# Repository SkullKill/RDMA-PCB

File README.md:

# RDMA-PCB
Rpi Dead Man Alarm - PCB and 3D case - Occupancy Monitoring - Raspberry Pi hat

24-RDMA-Case-04.jpg

23-RDMA-Case-03.jpg

07-RDMAweb-02.jpg

Video of it in action

## V 1.0 29/05/2020 - Initial Release

  ------------------------------------------------------------
## PCB Board Used

Ready to use PCB Board

https://www.skstore.com.au/electronics/pcb/RDMA

PCB Design Files / gerber files

[RDMA-PCB](https://github.com/SkullKill/RDMA-PCB)

3D Printed Case design files / STL

[RDMA-PCB](https://github.com/SkullKill/RDMA-PCB)

https://www.thingiverse.com/thing:4406335

https://www.myminifactory.com/object/3d-print-123446

FYI Gerber files are in the release section

https://github.com/SkullKill/RDMA-PCB/releases

more pictures in the wiki

https://github.com/SkullKill/RDMA-PCB/wiki

18-RDMA-Wiring-01.jpg

10-RDMA-FrontR-V1.0.jpg

15-RDMA-Back-BoardOnly-V1.0.jpg

  ------------------------------------------------------------
## Schematics

09-RDMA-schematics-v1.0.jpg

  ------------------------------------------------------------
## MecanicalDrawing

1 to 1 scale 

https://github.com/SkullKill/RDMA-PCB/blob/master/Case/RDMAcase-MecanicalDrawing-V1.0.pdf

please use PDF version, and print to scale

  ------------------------------------------------------------
## Code Used

[RDMA](https://github.com/SkullKill/RDMA)

  ------------------------------------------------------------

PCB features

* Step down DC DC regulator (12v will power both the pi and PIR sensor)
* Input has a self reset fuse, and reverse polarity protection.
* Physical on/off switch when powered via 12v
* Back power protection to allow pi to provide power.
* RTC clock
* Segment display (to display time left before alarm is triggered)
* Ability to trigger 3 X 5V object (e.g buzzer or lights) (will probably only populate one for the buzzer)
* The above trigger can be set to either 5V or 12V.
* Built in buzzer (to alert operator 1 min before alarm is triggered and SMS are sent out)
* 1-wire rail (possibility to add a number of DS18B20 temperature sensors)
* 2 physical button, one to manually reset the timer, or if hold for a few sec, will extend the timer once. Other button is to shutdown/unused.
* Ability to add external buttons.
* 1 configurable status light. (on when the service is running)
* All button, including PIR input has a physical denounce to eliminate noise/false alarm.
* EEPROM as per pi hat requirement (will probably not populate)
* Screw terminal for all connectors. No crimping required.

---------------------------

A 12V , 1A PSU should work, however, to be on the safe side, use a 12V, 2A PSU

Standard wall mount sensor DG65
https://www.paradox.com/Products/default.asp?CATID=8&SUBCATID=79&PRD=1389

swivel mount for DG65
https://www.paradox.com/Products/default.asp?CATID=8&SUBCATID=81&PRD=456

---------------------------

if the service is not running after restarting, GPIO 8 would be on, which would make the buzzer turn on. to turn it off, use the following.

    gpio readall
    gpio -g mode 8 output
    gpio -g write 8 0

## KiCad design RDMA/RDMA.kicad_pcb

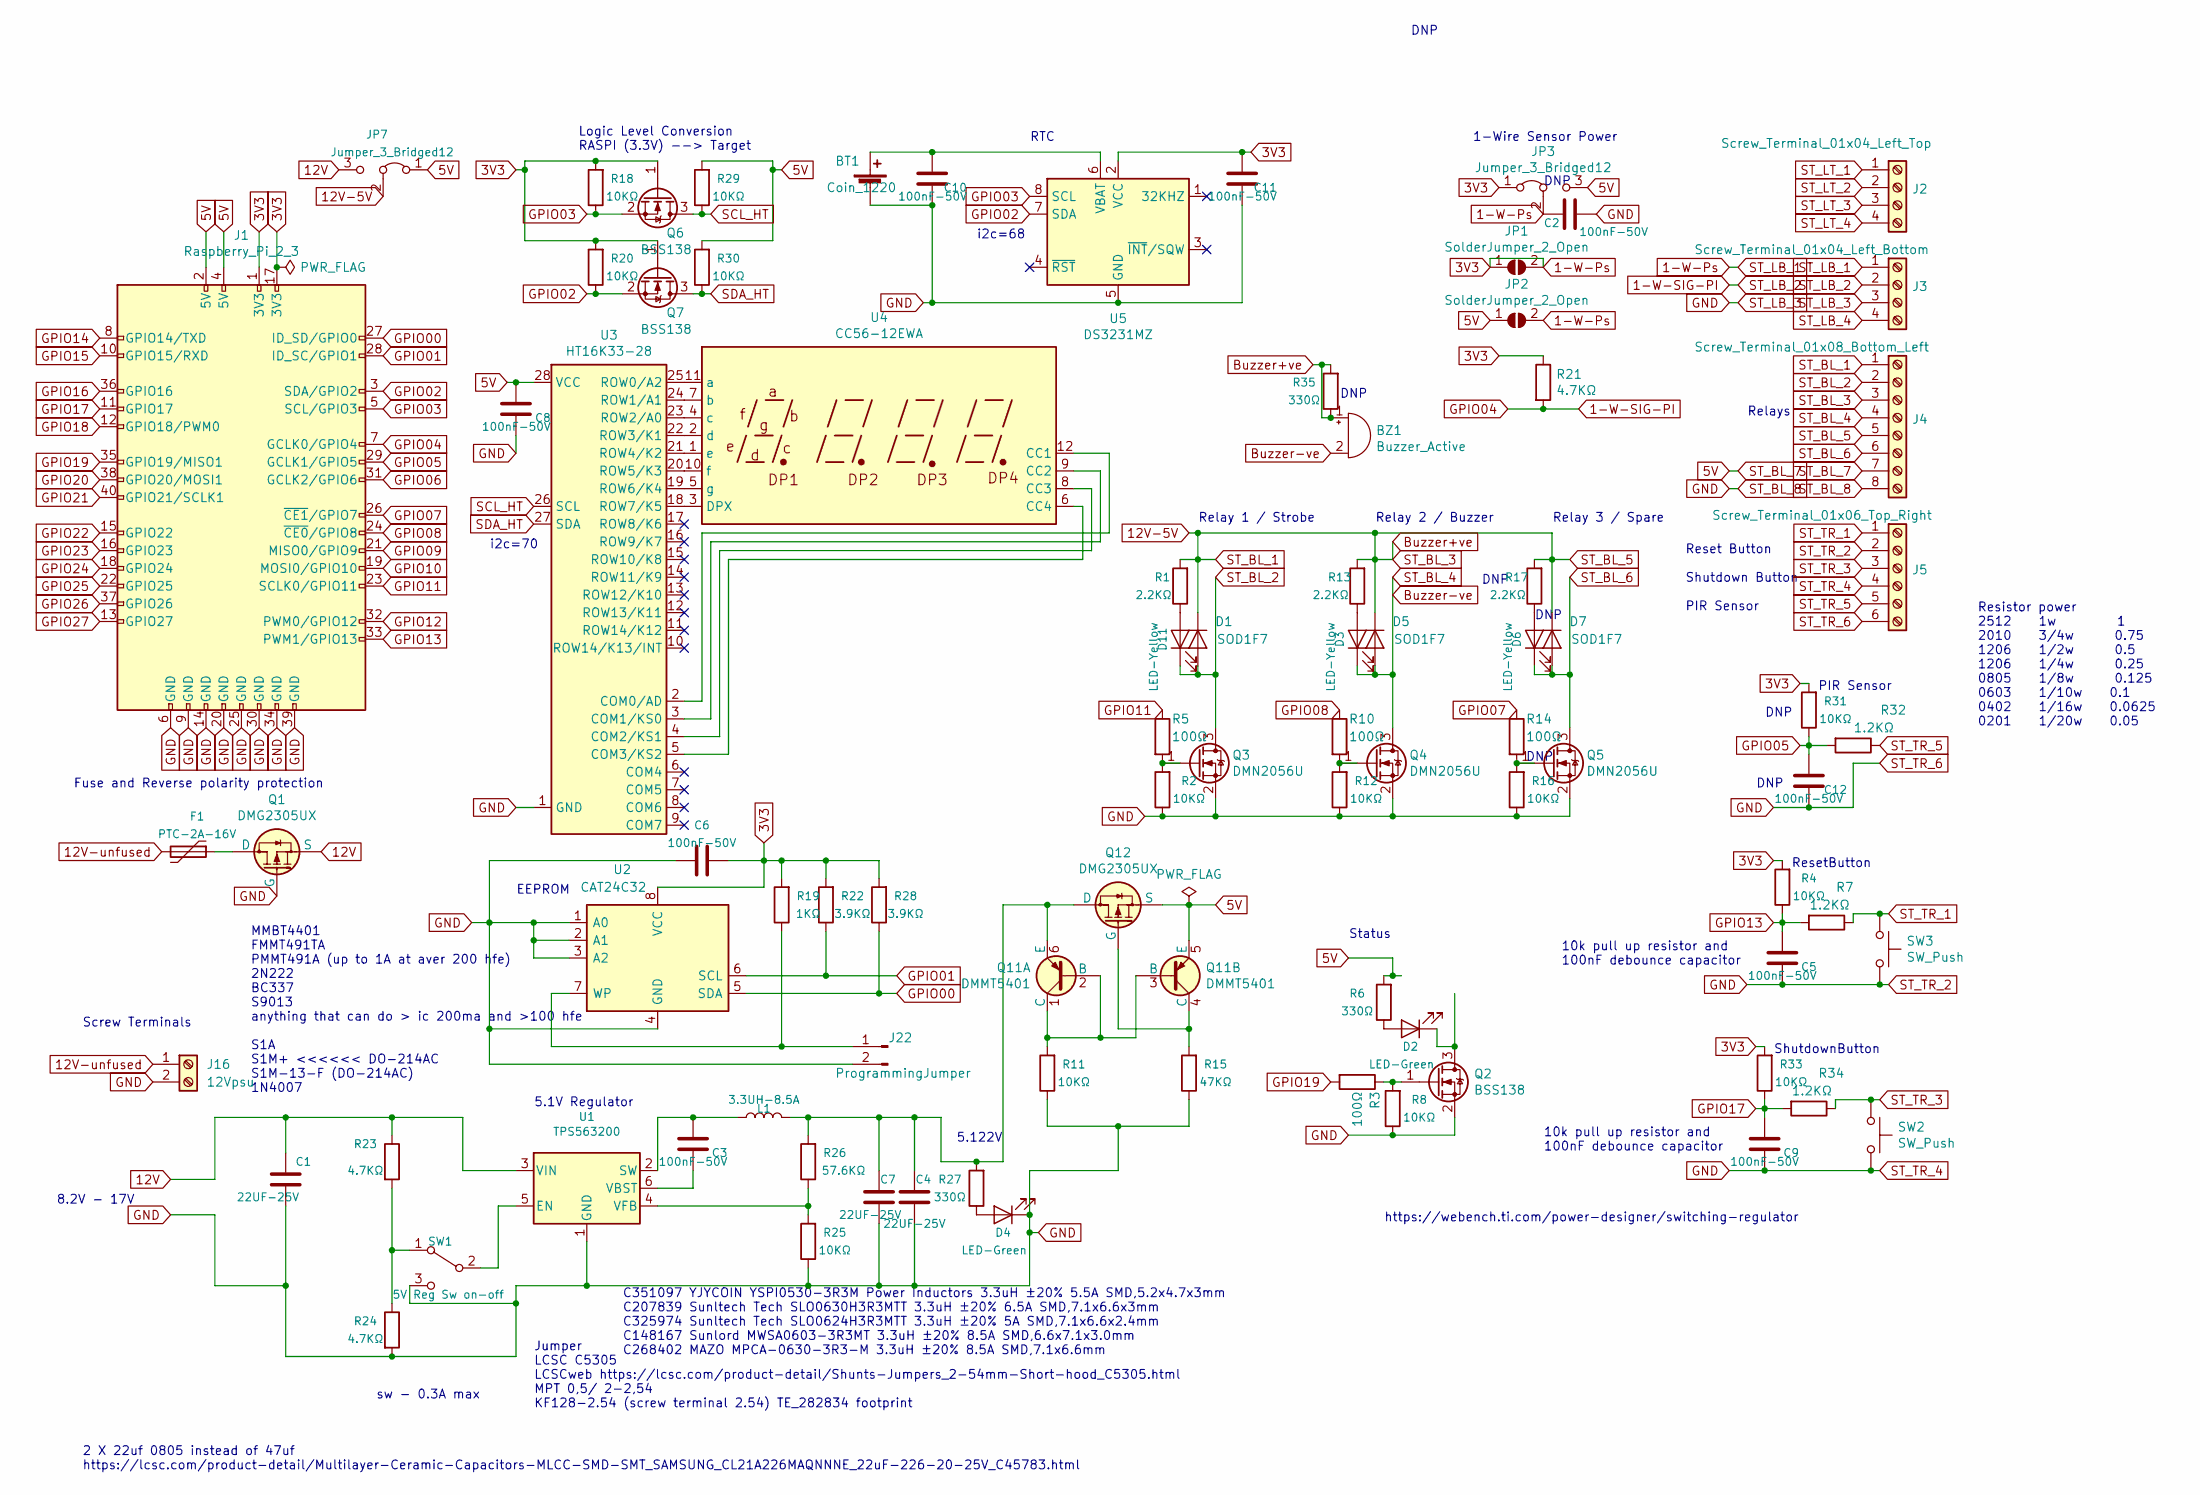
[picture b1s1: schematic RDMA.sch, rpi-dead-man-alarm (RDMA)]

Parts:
BT1: Coin_1220; BatteryHolder_Keystone_1056_1x1220; MPN CR1220-2; LCSC C70381
BZ1: Buzzer_Active; Buzzer_9x5.5RM5.0; MPN HNB09A05; LCSC C96493
C1, C4, C7: 22UF-25V; C_0805_2012Metric; MPN CL21A226MAQNNNE; LCSC C45783
C2, C3, C5, C6, C8, C9, C10, C11, C12: 100nF-50V; C_0603_1608Metric; MPN AC0603KRX7R9BB104; LCSC C149620
D1, D5, D7: SOD1F7; D_SOD-123; MPN SOD1F7; LCSC C33221
D2, D4: LED-Green; LED_0603_1608Metric; MPN ORH-G36G; LCSC C205443
D3, D6, D11: LED-Yellow; LED_0603_1608Metric; MPN FC-DA1608HYK-588J; LCSC C84268
F1: PTC-2A-16V; Fuse_1812_4532Metric_Pad1.30x3.40mm_HandSolder; MPN SCF200-16-1812R; LCSC C305617
J1: Raspberry_Pi_2_3; PinSocket_2x20_P2.54mm_Vertical; LCSC C50982
J2: Screw_Terminal_01x04_Left_Top; TerminalBlock_TE_282834-4_1x04_P2.54mm_Horizontal; MPN KF128-2.54-4P
J3: Screw_Terminal_01x04_Left_Bottom; TerminalBlock_TE_282834-4_1x04_P2.54mm_Horizontal; MPN KF128-2.54-4P
J4: Screw_Terminal_01x08_Bottom_Left; TerminalBlock_TE_282834-8_1x08_P2.54mm_Horizontal; MPN KF128-2.54-8P
J5: Screw_Terminal_01x06_Top_Right; TerminalBlock_TE_282834-6_1x06_P2.54mm_Horizontal; MPN KF128-2.54-6P
J16: 12Vpsu; TerminalBlock_bornier-2_P5.08mm; MPN WJ126V-5.0-2P; LCSC C8404
J22: ProgrammingJumper; PinHeader_1x02_P2.54mm_Vertical; LCSC C124375
JP1, JP2: SolderJumper_2_Open; R_0805_2012Metric; MPN RC0805JR-070RL; LCSC C96345
JP3, JP7: Jumper_3_Bridged12; PinHeader_1x03_P2.54mm_Vertical; LCSC C49257
L1: 3.3UH-8.5A; L_6.3x6.3_H3_HandSolder; MPN MPCA-0630-3R3-M; LCSC C268402
Q1, Q12: DMG2305UX; SOT-23; MPN DMG2305UX-13; LCSC C144153
Q2, Q6, Q7: BSS138; SOT-23; MPN BSS138-7-F; LCSC C40912
Q3, Q4, Q5: DMN2056U; SOT-23; MPN DMN2056U-7; LCSC C332302
Q11: DMMT5401; SOT-23-6; MPN DMMT5401-7-F; LCSC C154733
R1, R13, R17: 2.2KΩ; R_0603_1608Metric; MPN RC0603FR-072K2L; LCSC C114662
R2, R4, R8, R11, R12, R16, R18, R20, R25, R29, R30, R31, R33: 10KΩ; R_0603_1608Metric; MPN RC0603FR-0710KL; LCSC C98220
R3, R5, R10, R14: 100Ω; R_0603_1608Metric; MPN RC0603FR-07100RL; LCSC C105588
R6, R27, R35: 330Ω; R_0603_1608Metric; MPN RC0603FR-07330RL; LCSC C105881
R7, R32, R34: 1.2KΩ; R_0603_1608Metric; MPN RC0603FR-071K2L; LCSC C114605
R15: 47KΩ; R_0603_1608Metric; MPN AC0603FR-0747KL; LCSC C111134
R19: 1KΩ; R_0603_1608Metric; MPN RC0603FR-071KL; LCSC C22548
R21, R23, R24: 4.7KΩ; R_0603_1608Metric; MPN RC0603FR-074K7L; LCSC C99782
R22, R28: 3.9KΩ; R_0603_1608Metric; MPN RC0603FR-073K9L; LCSC C114616
R26: 57.6KΩ; R_0603_1608Metric; MPN RC0603FR-0757K6L; LCSC C245983
SW1: 5V Reg Sw on-off; SW_SPDT_PCM12; MPN K3-1292S-P2; LCSC C145853
SW2, SW3: SW_Push; SW_SPST_TL3305A; LCSC C174049
U1: TPS563200; SOT-23-6_Handsoldering; MPN TPS563200DDCR; LCSC C97253
U2: CAT24C32; SOIC-8_3.9x4.9mm_P1.27mm; MPN CAT24C32WI-GT3; LCSC C81193
U3: HT16K33-28; SOIC-28W_7.5x17.9mm_P1.27mm; LCSC C87502
U4: CC56-12EWA; CA56-12EWA; LCSC C10709
U5: DS3231MZ; SOIC-8_3.9x4.9mm_P1.27mm; MPN DS3231MZ+TRL; LCSC C107410

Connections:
1-W-Ps: C2.2, C6.2, C11.2, J1.1 (3V3), J1.17 (3V3), J3.1, JP1.1 (A), JP1.2 (B), JP2.2 (B), JP3.1 (A), JP3.2 (C), Q6.1 (G), Q7.1 (G), R4.2, R18.2, R19.2, R20.2, R21.1, R22.2, R28.2, R31.2, R33.2, U2.8 (VCC), U5.2 (VCC)
1-W-SIG-PI: J1.7 (GCLK0/GPIO4), J3.2, R21.2
5V: C8.2, J1.2 (5V), J1.4 (5V), J4.7, JP2.1 (A), JP3.3 (B), JP7.1 (A), Q11.5 (E), Q12.2 (S), R6.2, R29.2, R30.2, U3.28 (VCC)
12V: C1.2, JP7.3 (B), Q1.2 (S), R23.1, U1.3 (VIN)
12V-5V: BZ1.1 (-), D1.1 (K), D5.1 (K), D7.1 (K), J4.1, J4.3, J4.5, JP7.2 (C), R1.2, R13.2, R17.2, R35.1, R35.2
12V-unfused: F1.2, J16.1
Buzzer-ve: BZ1.2 (+), D3.1 (K), D5.2 (A), J4.4, Q4.3 (D)
GND: BT1.2 (-), C1.1, C2.1, C4.2, C5.2, C6.1, C7.1, C8.1, C9.2, C10.1, C11.1, C12.2, D4.1 (K), J1.6 (GND), J1.9 (GND), J1.14 (GND), J1.20 (GND), J1.25 (GND), J1.30 (GND), J1.34 (GND), J1.39 (GND), J3.3, J4.8, J5.2, J5.4, J5.6, J16.2, J22.2, Q1.1 (G), Q2.2 (S), Q3.2 (S), Q4.2 (S), Q5.2 (S), R2.1, R8.1, R11.1, R12.1, R15.1, R16.1, R24.2, R25.1, SW1.3 (C), SW2.2, SW3.2, U1.1 (GND), U2.1 (A0), U2.2 (A1), U2.3 (A2), U2.4 (GND), U3.1 (GND), U5.5 (GND)
GPIO00: J1.27 (ID_SD/GPIO0), R28.1, U2.5 (SDA)
GPIO01: J1.28 (ID_SC/GPIO1), R22.1, U2.6 (SCL)
GPIO02: J1.3 (SDA/GPIO2), Q7.2 (S), R20.1, U5.7 (SDA)
GPIO03: J1.5 (SCL/GPIO3), Q6.2 (S), R18.1, U5.8 (SCL)
GPIO05: C12.1, J1.29 (GCLK1/GPIO5), R31.1, R32.2
GPIO06: J1.31 (GCLK2/GPIO6)
GPIO07: J1.26 (~CE1~/GPIO7), R14.1
GPIO08: J1.24 (~CE0~/GPIO8), R10.1
GPIO09: J1.21 (MISO0/GPIO9)
GPIO10: J1.19 (MOSI0/GPIO10)
GPIO11: J1.23 (SCLK0/GPIO11), R5.1
GPIO12: J1.32 (PWM0/GPIO12)
GPIO13: C5.1, J1.33 (PWM1/GPIO13), R4.1, R7.2
GPIO14: J1.8 (GPIO14/TXD)
GPIO15: J1.10 (GPIO15/RXD)
GPIO16: J1.36 (GPIO16)
GPIO17: C9.1, J1.11 (GPIO17), R33.1, R34.2
GPIO18: J1.12 (GPIO18/PWM0)
GPIO19: J1.35 (GPIO19/MISO1), R3.2
GPIO20: J1.38 (GPIO20/MOSI1)
GPIO21: J1.40 (GPIO21/SCLK1)
GPIO22: J1.15 (GPIO22)
GPIO23: J1.16 (GPIO23)
GPIO24: J1.18 (GPIO24)
GPIO25: J1.22 (GPIO25)
GPIO26: J1.37 (GPIO26)
GPIO27: J1.13 (GPIO27)
unnamed: BT1.1 (+), C10.2, U5.6 (VBAT)
unnamed: C3.1, L1.1, U1.2 (SW)
unnamed: C3.2, U1.6 (VBST)
unnamed: C4.1, C7.2, L1.2, Q11.6 (E), Q12.3 (D), R26.2, R27.2
unnamed: D2.1 (K), Q2.3 (D)
unnamed: D2.2 (A), R6.1
unnamed: D3.2 (A), R13.1
unnamed: D4.2 (A), R27.1
unnamed: D6.2 (A), R17.1
unnamed: D11.2 (A), R1.1
unnamed: F1.1, Q1.3 (D)
unnamed: J22.1, R19.1, U2.7 (WP)
unnamed: Q2.1 (G), R3.1, R8.2
unnamed: Q3.1 (G), R2.2, R5.2
unnamed: Q4.1 (G), R10.2, R12.2
unnamed: Q5.1 (G), R14.2, R16.2
unnamed: Q11.1 (C), Q11.2 (B), Q11.3 (B), R11.2
unnamed: Q11.4 (C), Q12.1 (G), R15.2
unnamed: R23.2, R24.1, SW1.1 (A)
unnamed: R25.2, R26.1, U1.4 (VFB)
unnamed: SW1.2 (B), U1.5 (EN)
unnamed: U3.2 (COM0/AD), U4.12 (CC1)
unnamed: U3.3 (COM1/KS0), U4.9 (CC2)
unnamed: U3.4 (COM2/KS1), U4.8 (CC3)
unnamed: U3.5 (COM3/KS2), U4.6 (CC4)
unnamed: U3.18 (ROW7/K5), U4.3 (DPX)
unnamed: U3.19 (ROW6/K4), U4.5 (g)
unnamed: U3.20 (ROW5/K3), U4.10 (f)
unnamed: U3.21 (ROW4/K2), U4.1 (e)
unnamed: U3.22 (ROW3/K1), U4.2 (d)
unnamed: U3.23 (ROW2/A0), U4.4 (c)
unnamed: U3.24 (ROW1/A1), U4.7 (b)
unnamed: U3.25 (ROW0/A2), U4.11 (a)
SCL_HT: Q6.3 (D), R29.1, U3.26 (SCL)
SDA_HT: Q7.3 (D), R30.1, U3.27 (SDA)
ST_BL_2: D1.2 (A), D11.1 (K), J4.2, Q3.3 (D)
ST_BL_6: D6.1 (K), D7.2 (A), J4.6, Q5.3 (D)
ST_LB_4: J3.4
ST_TR_1: J5.1, R7.1, SW3.1
ST_TR_3: J5.3, R34.1, SW2.1
ST_TR_5: J5.5, R32.1

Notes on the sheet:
Screw Terminals
https://webench.ti.com/power-designer/switching-regulator
10k pull up resistor and 100nF debounce capacitor
5.122V
5.1V Regulator
8.2V - 17V
sw - 0.3A max
Fuse and Reverse polarity protection
Status
Relay 1 / Strobe
Relay 2 / Buzzer
Relay 3 / Spare
ResetButton
Relays
Reset Button Shutdown Button PIR Sensor
1-Wire Sensor Power
ShutdownButton
DNP
PIR Sensor
RTC
Logic Level Conversion RASPI (3.3V) --> Target
i2c=68
i2c=70
Resistor power 2512 1w 1 2010 3/4w 0.75 1206 1/2w 0.5 1206 1/4w 0.25 0805 1/8w 0.125 0603 1/10w 0.1 0402 1/16w 0.0625 0201 1/20w 0.05
MMBT4401 FMMT491TA PMMT491A (up to 1A at aver 200 hfe) 2N222 BC337 S9013 anything that can do > ic 200ma and >100 hfe S1A S1M+ <<<<<< DO-214AC S1M-13-F (DO-214AC) 1N4007
C351097 YJYCOIN YSPI0530-3R3M Power Inductors 3.3uH ±20% 5.5A SMD,5.2x4.7x3mm C207839 Sunltech Tech SLO0630H3R3MTT 3.3uH ±20% 6.5A SMD,7.1x6.6x3mm C325974 Sunltech Tech SLO0624H3R3MTT 3.3uH ±20% 5A SMD,7.1x6.6x2.4mm C148167 Sunlord MWSA0603-3R3MT 3.3uH ±20% 8.5A SMD,6.6x7.1x3.0mm C268402 MAZO MPCA-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
2 X 22uf 0805 instead of 47uf https://lcsc.com/product-detail/Multilayer-Ceramic-Capacitors-MLCC-SMD-SMT_SAMSUNG_CL21A226MAQNNNE_22uF-226-20-25V_C45783.html
Jumper LCSC C5305 LCSCweb https://lcsc.com/product-detail/Shunts-Jumpers_2-54mm-Short-hood_C5305.html MPT 0,5/ 2-2,54 KF128-2.54 (screw terminal 2.54) TE_282834 footprint
EEPROM

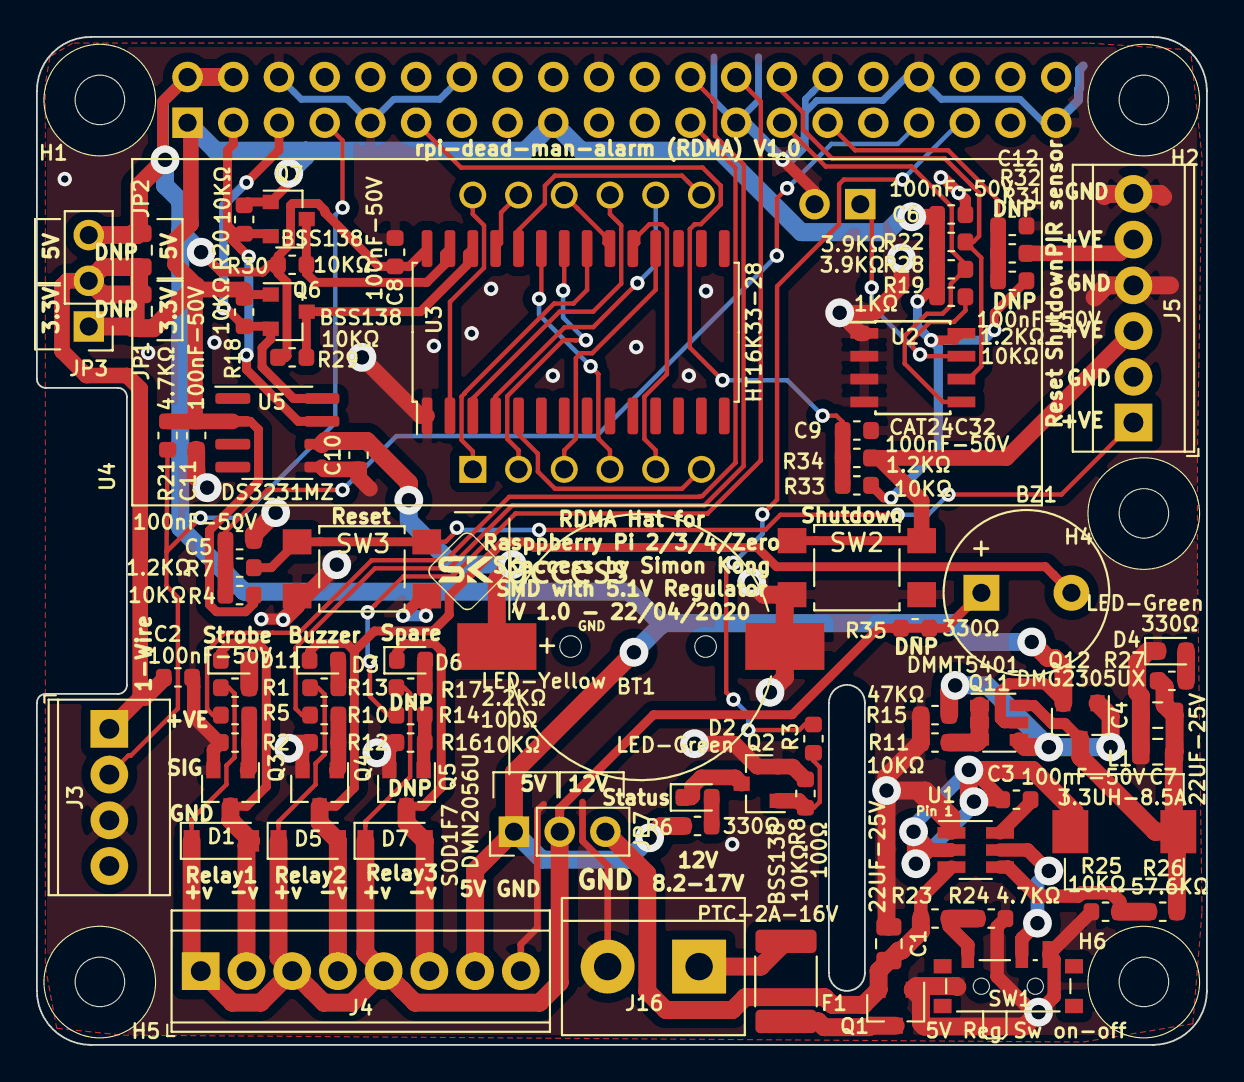
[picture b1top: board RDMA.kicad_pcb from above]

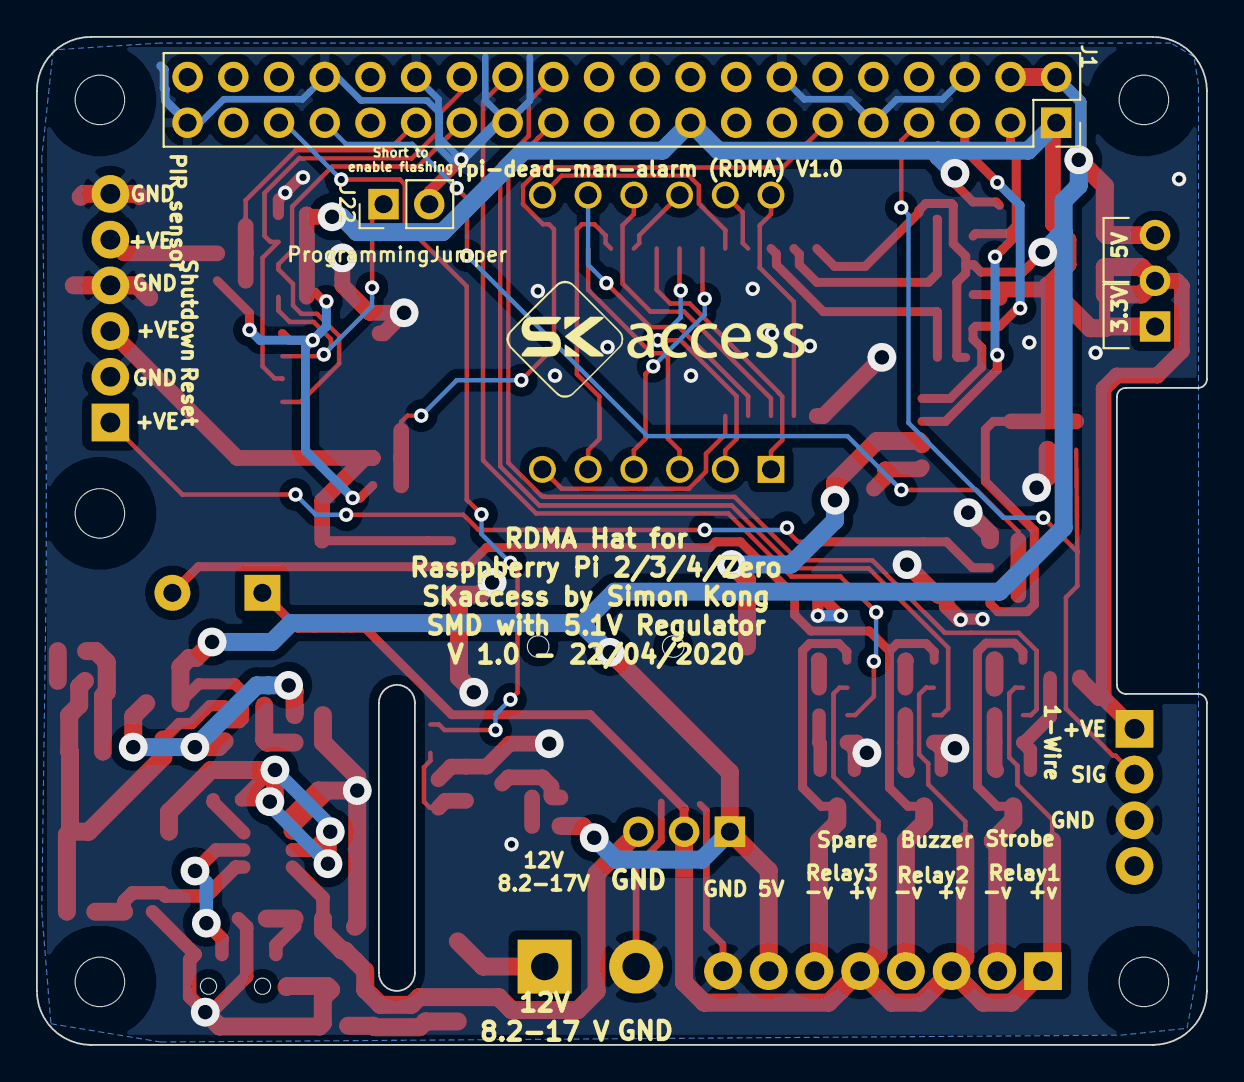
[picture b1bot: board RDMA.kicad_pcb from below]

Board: 2 copper layers, 65.0 x 56.0 mm, 90 parts (2 on the bottom side), 59 nets.

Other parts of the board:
H1, H2, H4, H5, H6: MountingHole; MountingHole_2.75mm_M2.5_NoPad

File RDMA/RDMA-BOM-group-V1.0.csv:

Reference, Quantity, Value, Footprint, Datasheet, Alt, LCSC, LCSCweb, MPN, ALT, MPNweb, web
BT1 ,1,Coin_1220,RDMA:BatteryHolder_Keystone_1056_1x1220,https://datasheet.lcsc.com/szlcsc/Q-J-CR1220-2_C70381.pdf,,C70381,https://lcsc.com/product-detail/Battery-Holders-Clips-Contac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,CR1220-2,C238067,,
BZ1 ,1,Buzzer_Active,RDMA:Buzzer_9x5.5RM5.0,https://datasheet.lcsc.com/szlcsc/1811141138_Jiangsu-Huaneng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,,C96493,https://lcsc.com/product-detail/Buzzers_Jiangsu-Huaneng-Elec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,HNB09A05,,,
C4 C1 C7 ,3,22UF-25V,Capacitor_SMD:C_0805_2012Metric,https://datasheet.lcsc.com/szlcsc/Samsung-Electro-Mechanics-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,,C45783,https://lcsc.com/product-detail/Multilayer-Ceramic-Capacitor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,CL21A226MAQNNNE,C86816,,
C5 C3 C6 C9 C2 C12 C10 C11 C8 ,(9-2)=7,100nF-50V,Capacitor_SMD:C_0603_1608Metric,https://datasheet.lcsc.com/szlcsc/YAGEO-AC0603KRX7R9BB104_C1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,,C149620,https://lcsc.com/product-detail/Multilayer-Ceramic-Capacitor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,AC0603KRX7R9BB104,,,
D1 D5 D7 ,(3-1)=2,SOD1F7,Diode_SMD:D_SOD-123,https://datasheet.lcsc.com/szlcsc/1903041730_MDD-Jiangsu-Yut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,,C33221,https://lcsc.com/product-detail/Diodes-Rectifiers-Fast-Recov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,SOD1F7,,,
D11 D3 D6 ,(3-1)=2,LED-Yellow,LED_SMD:LED_0603_1608Metric,https://datasheet.lcsc.com/szlcsc/Foshan-NationStar-Optoelec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,,C84268,https://lcsc.com/product-detail/Light-Emitting-Diodes-LED_Ye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,FC-DA1608HYK-588J,,,
D4 D2 ,2,LED-Green,LED_SMD:LED_0603_1608Metric,https://datasheet.lcsc.com/szlcsc/Orient-ORH-G36G_C205443.pdf,,C205443,https://lcsc.com/product-detail/Light-Emitting-Diodes-LED_06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,ORH-G36G,,,
F1 ,1,PTC-2A-16V,Fuse:Fuse_1812_4532Metric_Pad1.30x3.40mm_HandSolder,https://datasheet.lcsc.com/szlcsc/SOCAY-Elec-SCF200-16-1812R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,,C305617,https://lcsc.com/product-detail/Others_SOCAY-Elec-SCF200-16-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,SCF200-16-1812R,,,
J1 ,1,Raspberry_Pi_2_3,Connector_PinSocket_2.54mm:PinSocket_2x20_P2.54mm_Vertical,https://www.raspberrypi.org/documentation/hardware/raspberry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,C35165,C50982,https://lcsc.com/product-detail/Pin-Header-Female-Header_Boo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,,,,
J16 ,1,12Vpsu,pi-template:TerminalBlock_bornier-2_P5.08mm,https://datasheet.lcsc.com/szlcsc/Ningbo-Kangnex-Elec-WJ126V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,,C8404,https://lcsc.com/product-detail/Pluggable-System-Terminal-Bl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,WJ126V-5.0-2P,,,
J2 ,1,Screw_Terminal_01x04_Left_Top,pi-template:TerminalBlock_TE_282834-4_1x04_P2.54mm_Horizontal,~,,,,KF128-2.54-4P,,http://en.cnkefa.com/index.php?c=product&id=159,https://www.aliexpress.com/store/group/Connection-terminal/4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
J22 ,1,ProgrammingJumper,Connector_PinHeader_2.54mm:PinHeader_1x02_P2.54mm_Vertical,~,,C124375,https://lcsc.com/product-detail/Pin-Header-Female-Header_She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,,,,
J3 ,1,Screw_Terminal_01x04_Left_Bottom,pi-template:TerminalBlock_TE_282834-4_1x04_P2.54mm_Horizontal,~,,,,KF128-2.54-4P,,http://en.cnkefa.com/index.php?c=product&id=159,https://www.aliexpress.com/store/group/Connection-terminal/4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
J4 ,1,Screw_Terminal_01x08_Bottom_Left,pi-template:TerminalBlock_TE_282834-8_1x08_P2.54mm_Horizontal,~,,,,KF128-2.54-8P,,http://en.cnkefa.com/index.php?c=product&id=159,
J5 ,1,Screw_Terminal_01x06_Top_Right,pi-template:TerminalBlock_TE_282834-6_1x06_P2.54mm_Horizontal,~,,,,KF128-2.54-6P,,http://en.cnkefa.com/index.php?c=product&id=159,
JP2 JP1 ,2,SolderJumper_2_Open,Resistor_SMD:R_0805_2012Metric,https://datasheet.lcsc.com/szlcsc/YAGEO-RC0805JR-070RL_C96345.pdf,,C96345,https://lcsc.com/product-detail/Chip-Resistor-Surface-Mount_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,RC0805JR-070RL,,,
JP3 JP7 ,2,Jumper_3_Bridged12,Connector_PinHeader_2.54mm:PinHeader_1x03_P2.54mm_Vertical,https://datasheet.lcsc.com/szlcsc/Boom-Precision-Elec-Header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,,C49257,https://lcsc.com/product-detail/Pin-Header-Female-Header_Boo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,,,,
L1 ,1,3.3UH-8.5A,pi-template:L_6.3x6.3_H3_HandSolder,https://datasheet.lcsc.com/szlcsc/1812181433_MAZO-MPCA-0630-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,,C268402,https://lcsc.com/product-detail/Others_MAZO-MPCA-0630-3R3-M_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,MPCA-0630-3R3-M,C207839,,
Q11 ,1,DMMT5401,Package_TO_SOT_SMD:SOT-23-6,https://datasheet.lcsc.com/szlcsc/Diodes-Incorporated-DMMT54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,,C154733,https://lcsc.com/product-detail/Transistors-NPN-PNP_DIODES_D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,DMMT5401-7-F,,,
Q12 Q1 ,2,DMG2305UX,Package_TO_SOT_SMD:SOT-23,https://datasheet.lcsc.com/szlcsc/Diodes-Incorporated-DMG230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,,C144153,https://lcsc.com/product-detail/MOSFET_Diodes-Incorporated_D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,DMG2305UX-13,,,
Q2 Q6 Q7 ,3,BSS138,Package_TO_SOT_SMD:SOT-23,https://datasheet.lcsc.com/szlcsc/Diodes-Incorporated-BSS138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,,C40912,https://lcsc.com/product-detail/MOSFET_Diodes-Incorporated_B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,BSS138-7-F,,,
Q3 Q4 Q5 ,3,DMN2056U,Package_TO_SOT_SMD:SOT-23,http://www.diodes.com/assets/Datasheets/DMN2056U.pdf,,C332302,https://lcsc.com/product-detail/MOSFET_Diodes-Incorporated_D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,DMN2056U-7,,,
R1 R13 R17 ,(3-1)=2,2.2KΩ,Resistor_SMD:R_0603_1608Metric,https://datasheet.lcsc.com/szlcsc/YAGEO-RC0603FR-072K2L_C114662.pdf,,C114662,https://lcsc.com/product-detail/Chip-Resistor-Surface-Mount_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,RC0603FR-072K2L,,,
R15 ,1,47KΩ,Resistor_SMD:R_0603_1608Metric,https://datasheet.lcsc.com/szlcsc/YAGEO-AC0603FR-0747KL_C111134.pdf,,C111134,https://lcsc.com/product-detail/Chip-Resistor-Surface-Mount_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,AC0603FR-0747KL,RC0603FR-0747KL,,
R19 ,(1-1)=0,1KΩ,Resistor_SMD:R_0603_1608Metric,https://datasheet.lcsc.com/szlcsc/YAGEO-RC0603FR-071KL_C22548.pdf,,C22548,https://lcsc.com/product-detail/Chip-Resistor-Surface-Mount_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,RC0603FR-071KL,,,
R21 R23 R24 ,3,4.7KΩ,Resistor_SMD:R_0603_1608Metric,https://datasheet.lcsc.com/szlcsc/YAGEO-RC0603FR-074K7L_C99782.pdf,,C99782,https://lcsc.com/product-detail/Chip-Resistor-Surface-Mount_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,RC0603FR-074K7L,,,
R22 R28 ,(2-2)=0,3.9KΩ,Resistor_SMD:R_0603_1608Metric,https://datasheet.lcsc.com/szlcsc/YAGEO-RC0603FR-073K9L_C114616.pdf,,C114616,https://lcsc.com/product-detail/Chip-Resistor-Surface-Mount_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,RC0603FR-073K9L,,,
R26 ,1,57.6KΩ,Resistor_SMD:R_0603_1608Metric,https://datasheet.lcsc.com/szlcsc/YAGEO-RC0603FR-0757K6L_C24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,,C245983,https://lcsc.com/product-detail/Others_YAGEO-RC0603FR-0757K6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,RC0603FR-0757K6L,,,
R27 R6 R35 ,(3-1)=2,330Ω,Resistor_SMD:R_0603_1608Metric,https://datasheet.lcsc.com/szlcsc/YAGEO-RC0603FR-07330RL_C10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,,C105881,https://lcsc.com/product-detail/Chip-Resistor-Surface-Mount_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,RC0603FR-07330RL,,,
R34 R32 R7 ,3,1.2KΩ,Resistor_SMD:R_0603_1608Metric,https://datasheet.lcsc.com/szlcsc/YAGEO-RC0603FR-071K2L_C114605.pdf,,C114605,https://lcsc.com/product-detail/Chip-Resistor-Surface-Mount_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,RC0603FR-071K2L,,,
R4 R25 R11 R2 R8 R12 R16 R33 R31 R18 R29 R20 R30 ,(13-2)=11,10KΩ,Resistor_SMD:R_0603_1608Metric,https://datasheet.lcsc.com/szlcsc/YAGEO-RC0603FR-0710KL_C98220.pdf,,C98220,https://lcsc.com/product-detail/Chip-Resistor-Surface-Mount_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,RC0603FR-0710KL,,,
R5 R3 R10 R14 ,(4-1)=3,100Ω,Resistor_SMD:R_0603_1608Metric,https://datasheet.lcsc.com/szlcsc/YAGEO-RC0603FR-07100RL_C10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,,C105588,https://lcsc.com/product-detail/Chip-Resistor-Surface-Mount_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,RC0603FR-07100RL,,,
SW1 ,1,5V Reg Sw on-off,Button_Switch_SMD:SW_SPDT_PCM12,https://datasheet.lcsc.com/szlcsc/Korean-Hroparts-Elec-K3-12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,,C145853,https://lcsc.com/product-detail/Toggle-Switches_Korean-Hropa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,K3-1292S-P2,,,
SW3 SW2 ,2,SW_Push,RDMA:SW_SPST_TL3305A,~,,C174049,https://lcsc.com/product-detail/Tactile-Switches_Switch-4-5-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,,,,
U1 ,1,TPS563200,Package_TO_SOT_SMD:SOT-23-6_Handsoldering,http://www.ti.com/lit/ds/symlink/tps563200.pdf,,C97253,https://lcsc.com/product-detail/DC-DC-Converters_TI_TPS56320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,TPS563200DDCR,,,
U2 ,(1-1)=0,CAT24C32,Package_SO:SOIC-8_3.9x4.9mm_P1.27mm,https://datasheet.lcsc.com/szlcsc/ON-Semicon-ON-CAT24C32WI-G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,,C81193,https://lcsc.com/product-detail/EEPROM_ON-Semicon_CAT24C32WI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,CAT24C32WI-GT3,,,
U3 ,1,HT16K33-28,Package_SO:SOIC-28W_7.5x17.9mm_P1.27mm,https://datasheet.lcsc.com/szlcsc/1811091023_Holtek-Semicon-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,,C87502,https://lcsc.com/product-detail/LED-Drivers_HT16K33_C87502.html,,,,
U4 ,1,CC56-12EWA,Display_7Segment:CA56-12EWA,http://www.kingbrightusa.com/images/catalog/SPEC/CA56-12EWA.pdf,,C10709,https://lcsc.com/product-detail/Led-Segment-Display_Made-in-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,,,,
U5 ,1,DS3231MZ,Package_SO:SOIC-8_3.9x4.9mm_P1.27mm,https://datasheet.lcsc.com/szlcsc/Maxim-Integrated-DS3231MZ_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,,C107410,https://lcsc.com/product-detail/Real-time-Clocks_MAXIM_DS323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,DS3231MZ+TRL,,,
